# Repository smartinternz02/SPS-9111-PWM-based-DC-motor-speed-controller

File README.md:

# SPS-9111-PWM-based-DC-motor-speed-controller
PWM based DC motor speed controller

Project demonstration: 
<a href='https://drive.google.com/file/d/19TFDyVIvyd4UyYGVN5APTEoN5e7t8SUv/view?usp=sharing'>https://drive.google.com/file/d/19TFDyVIvyd4UyYGVN5APTEoN5e7t8SUv/view?usp=sharing</a>

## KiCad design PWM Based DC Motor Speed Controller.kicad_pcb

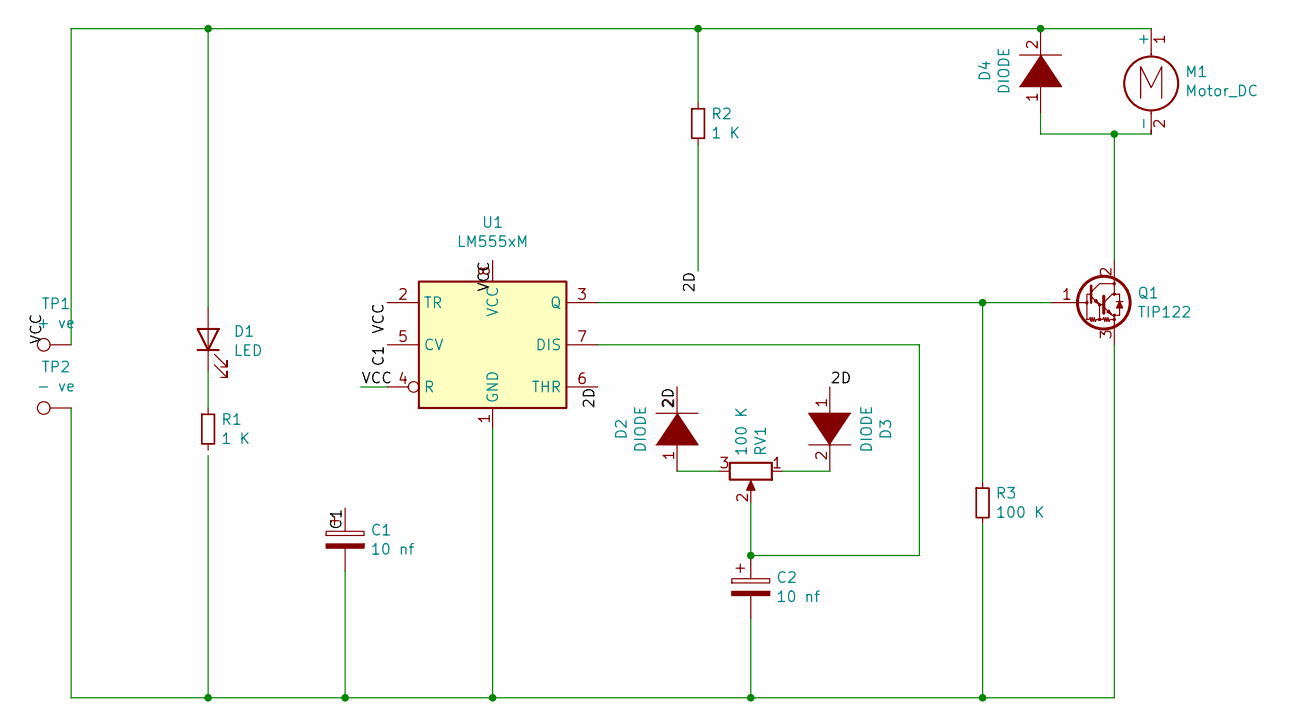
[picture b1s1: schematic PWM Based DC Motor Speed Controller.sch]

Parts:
C1, C2: 10 nf; C_2220_5650Metric_Pad1.97x5.40mm_HandSolder
D1: LED; LED_1206_3216Metric
D2, D3, D4: DIODE; D_0805_2012Metric
M1: Motor_DC; LED_D1.8mm_W3.3mm_H2.4mm
Q1: TIP122; TO-220-3_Vertical
R1, R2: 1 K; R_1206_3216Metric
R3: 100 K; R_1206_3216Metric
RV1: 100 K; Potentiometer_Bourns_3269W_Vertical
TP1: + ve; TestPoint_Loop_D3.50mm_Drill1.4mm_Beaded
TP2: - ve; TestPoint_Loop_D3.50mm_Drill1.4mm_Beaded
U1: LM555xM; SOIC-8_3.9x4.9mm_P1.27mm

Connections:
/2D: D2.2 (A), D3.1 (K), R2.2, U1.6 (THR)
/C1: C1.1, U1.5 (CV)
/VCC: U1.2 (TR), U1.4 (R), U1.8 (VCC)
unnamed: C1.2, C2.2, Q1.3 (E), R3.2, TP2.1, U1.1 (GND)
unnamed: C2.1, RV1.2, U1.7 (DIS)
unnamed: D1.1 (K), R1.1
unnamed: D1.2 (A), D4.2 (A), M1.1 (+), R2.1, TP1.1
unnamed: D2.1 (K), RV1.3
unnamed: D3.2 (A), RV1.1
unnamed: D4.1 (K), M1.2 (-), Q1.2 (C)
unnamed: Q1.1 (B), R3.1, U1.3 (Q)

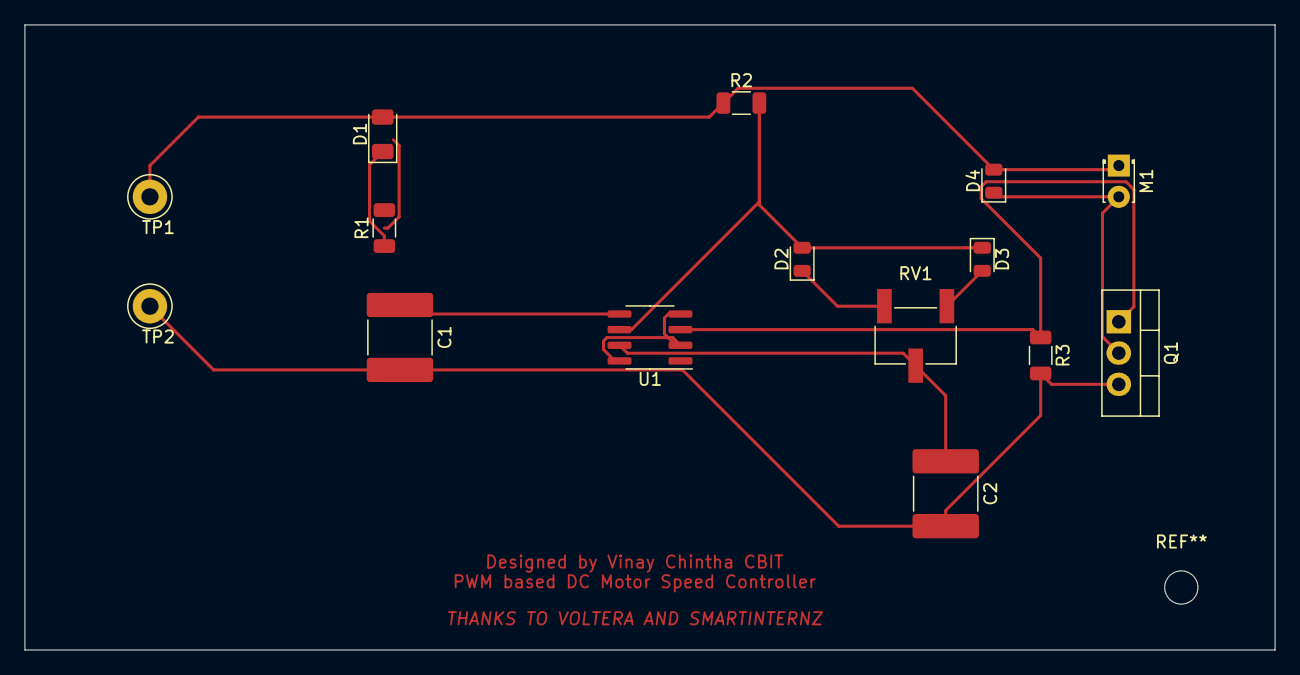
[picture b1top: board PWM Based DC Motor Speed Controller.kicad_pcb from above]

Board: 2 copper layers, 101.6 x 50.8 mm, 15 parts (0 on the bottom side), 11 nets.

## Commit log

2021-03-21 Add files via upload
    Electronic Product Build-A-Thon
    Unique program to build skills in Electronic Product Development.
2021-03-21 Add files via upload
    DOCUMENTATION
2021-03-21 Add files via upload
    DOCUMENTATION DOC
2021-03-22 Add files via upload
    PROJECT DEMONSTRATION
